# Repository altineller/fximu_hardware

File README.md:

### fximu_hardware

Hardware files for FXIMU project.

**Project main repository: https://github.com/altineller/fximu**

**Project firmware repository: https://github.com/altineller/fximu_firmware**  

---
|   ||
|----|----|

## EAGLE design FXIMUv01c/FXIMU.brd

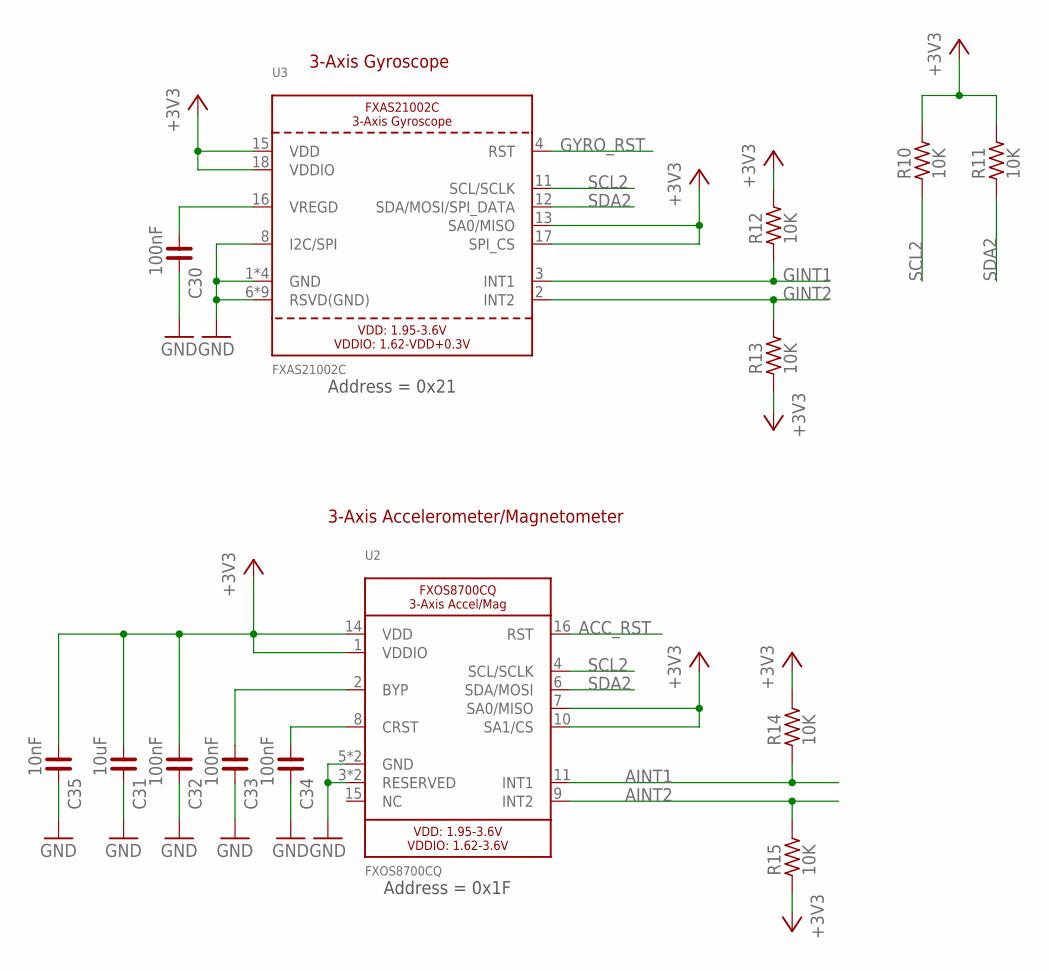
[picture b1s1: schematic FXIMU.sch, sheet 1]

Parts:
C30, C32, C33, C34: 100nF; C0402
C31: 10uF; C0603
C35: 10nF; C0402
R10, R11, R12, R13, R14, R15: 10K; R0402
U2: FXOS8700CQ; QFN16_3MM_FREESCALE_5X3
U3: FXAS21002C; QFN24_4MM_FREESCALE_7X5

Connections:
+3V3: C31.1, C32.1, C35.1, R10.2, R11.2, R12.2, R13.1, R14.2, R15.1, U2.1 (VDDIO), U2.7 (SA0/MISO), U2.10 (SA1/CS), U2.14 (VDD), U3.13 (SA0/MISO), U3.15 (VDD), U3.17 (SPI_CS), U3.18 (VDDIO); also elsewhere on the board
ACC_RST: U2.16 (RST); also elsewhere on the board
AINT1: R14.1, U2.11 (INT1); also elsewhere on the board
AINT2: R15.2, U2.9 (INT2); also elsewhere on the board
GINT1: R12.1, U3.3 (INT1); also elsewhere on the board
GINT2: R13.2, U3.2 (INT2); also elsewhere on the board
GND: C30.2, C31.2, C32.2, C33.2, C34.2, C35.2, U2.3 (RESERVED), U2.5 (GND), U2.12 (GND), U2.13 (RESERVED), U3.1 (GND), U3.5 (GND), U3.6 (RSVD(GND)), U3.7 (RSVD(GND)), U3.8 (I2C/SPI), U3.9 (RSVD(GND)), U3.10 (RSVD(GND)), U3.14 (GND), U3.19 (GND), U3.20 (RSVD(GND)), U3.21 (RSVD(GND)), U3.22 (RSVD(GND)), U3.23 (RSVD(GND)), U3.24 (RSVD(GND)); also elsewhere on the board
GYRO_RST: U3.4 (RST); also elsewhere on the board
unnamed: C30.1, U3.16 (VREGD)
unnamed: C33.1, U2.2 (BYP)
unnamed: C34.1, U2.8 (CRST)
SCL2: R10.1, U2.4 (SCL/SCLK), U3.11 (SCL/SCLK); also elsewhere on the board
SDA2: R11.1, U2.6 (SDA/MOSI), U3.12 (SDA/MOSI/SPI_DATA); also elsewhere on the board

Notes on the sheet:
Address = 0x21
Address = 0x1F
3-Axis Accelerometer/Magnetometer
3-Axis Gyroscope

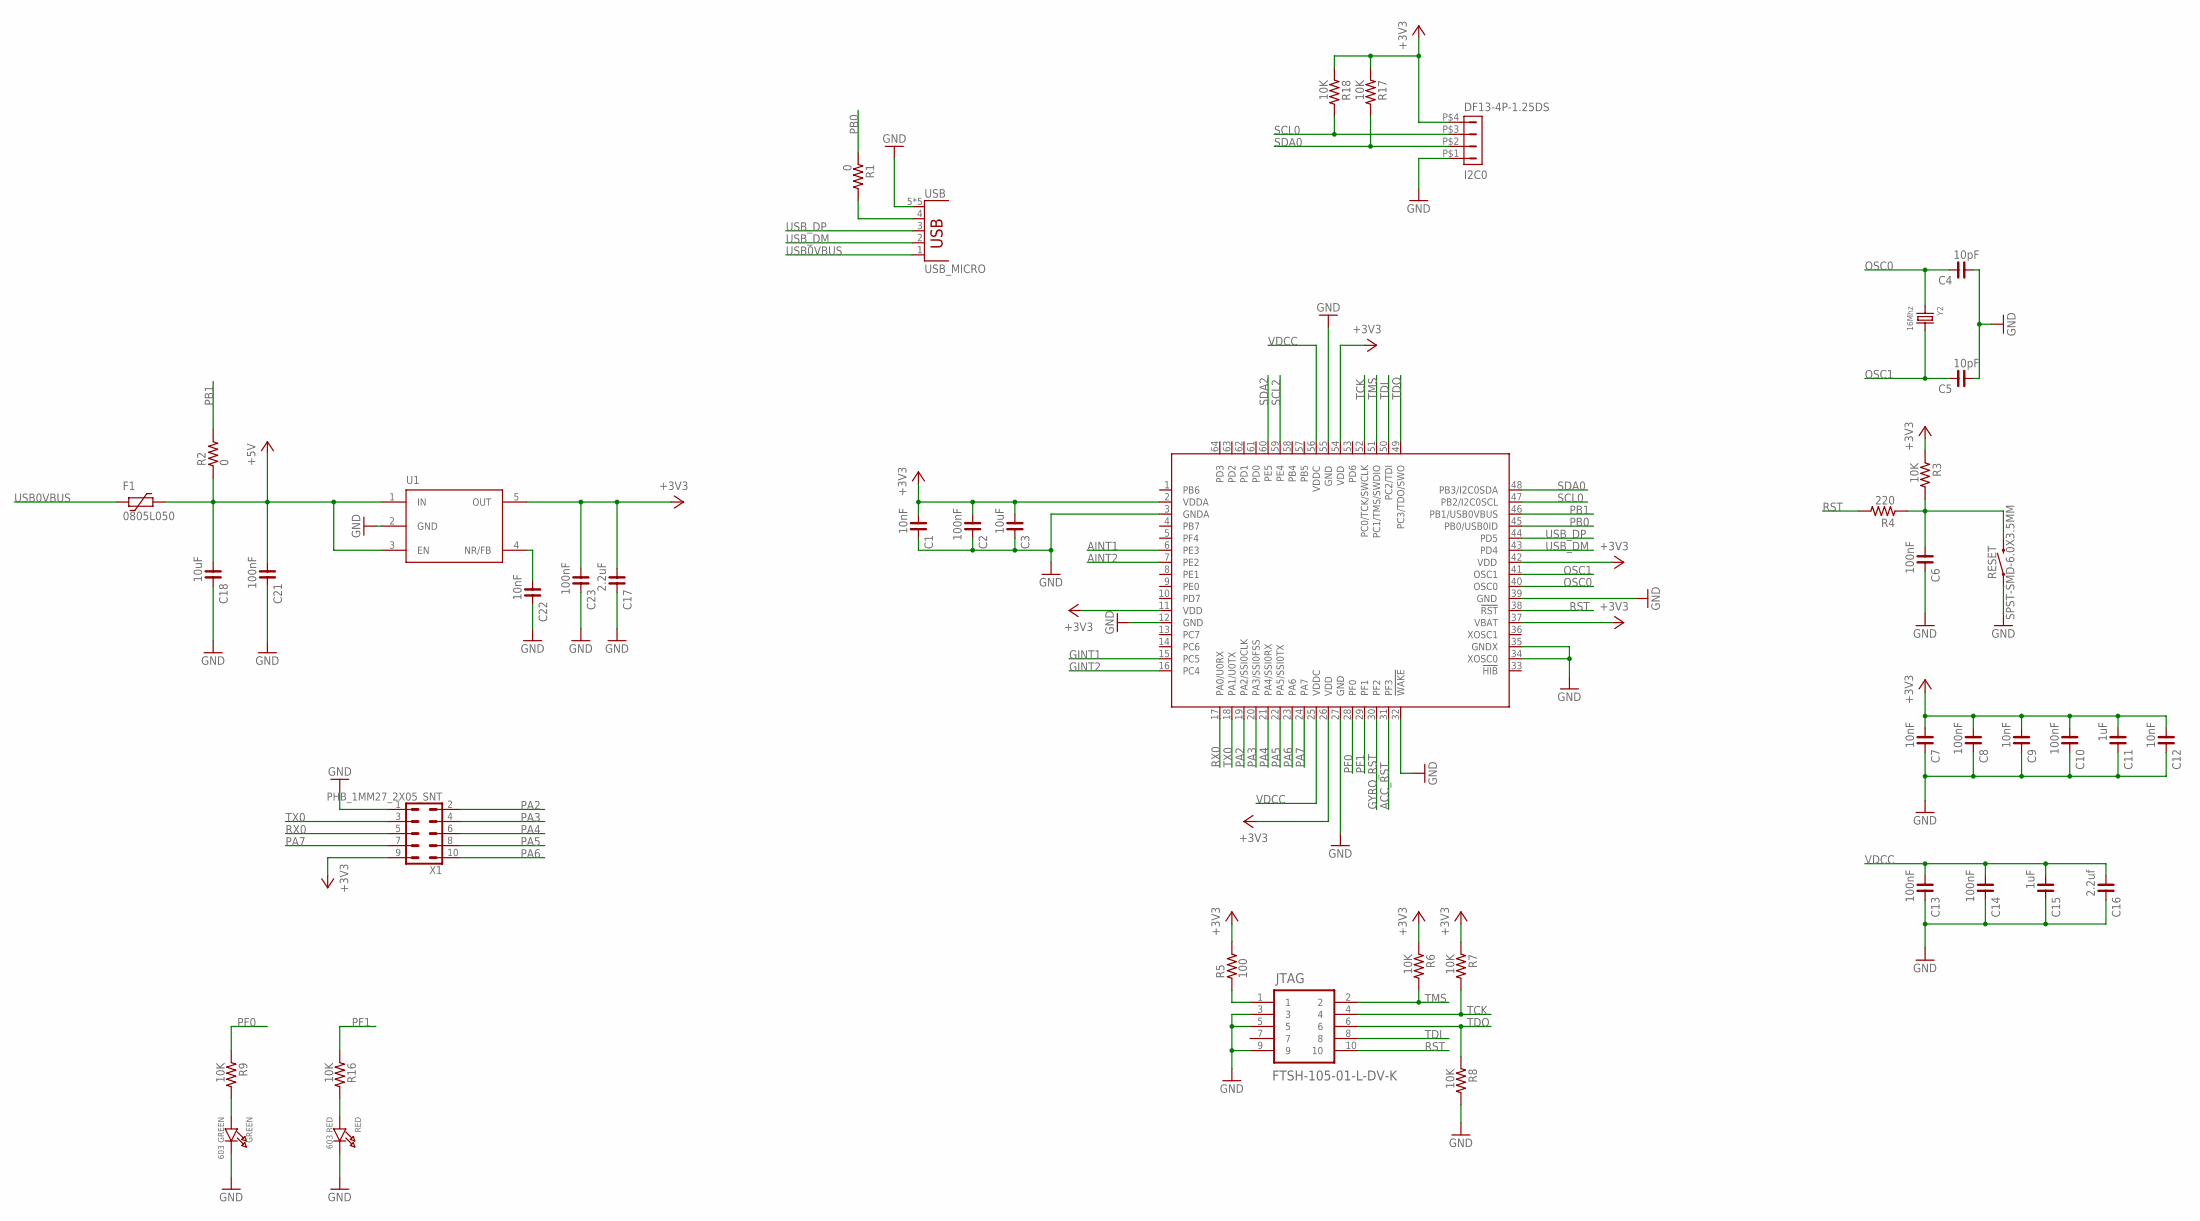
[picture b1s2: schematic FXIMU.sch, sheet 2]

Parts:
C1, C7, C9, C12, C22: 10nF; C0402
C2, C6, C8, C10, C13, C14, C21, C23: 100nF; C0402
C3, C18: 10uF; C0603
C4, C5: 10pF; C0402
C11, C15: 1uF; C0402
C16: 2.2uf; C0603
C17: 2.2uF; C0603
F1: 0805L050; 0805L
GREEN: 603 GREEN; CHIPLED_0603
I2C0: DF13-4P-1.25DS
IC1: TM4C123[7,G]XXPM; PM_S-PQFP-G64
JTAG: FTSH-105-01-L-DV-K; SAMTEC_FTSH-105-01-L-DV-K
R1, R2: 0; R0402
R3, R6, R7, R8, R9, R16, R17, R18: 10K; R0402
R4: 220; R0402
R5: 100; R0402
RED: 603 RED; CHIPLED_0603
RESET: SPST-SMD-6.0X3.5MM; TACTILE_SWITCH_SMD_6.0X3.5MM
U1: TPS73633; SOT23-5L
USB: USB_MICRO; USB_MICRO_MOLEX_FULL
X1: PHB_1MM27_2X05_SNT
Y2: 16Mhz; 6X3.3MM

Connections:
+3V3: C1.1, C2.1, C3.1, C7.1, C8.1, C9.1, C10.1, C11.1, C12.1, C17.1, C23.1, I2C0.P$4 (4), IC1.2 (VDDA), IC1.11 (VDD), IC1.26 (VDD), IC1.37 (VBAT), IC1.42 (VDD), IC1.54 (VDD), R3.1, R5.2, R6.1, R7.1, R17.1, R18.1, U1.5 (OUT), X1.9; also elsewhere on the board
+5V: C18.1, C21.1, F1.1, R2.1, U1.1 (IN), U1.3 (EN)
ACC_RST: IC1.31 (PF3); also elsewhere on the board
AINT1: IC1.6 (PE3); also elsewhere on the board
AINT2: IC1.7 (PE2); also elsewhere on the board
GINT1: IC1.15 (PC5); also elsewhere on the board
GINT2: IC1.16 (PC4); also elsewhere on the board
GND: C1.2, C2.2, C3.2, C4.1, C5.1, C6.2, C7.2, C8.2, C9.2, C10.2, C11.2, C12.2, C13.2, C14.2, C15.2, C16.2, C17.2, C18.2, C21.2, C22.2, C23.2, GREEN.C, I2C0.P$1 (1), IC1.3 (GNDA), IC1.12 (GND), IC1.27 (GND), IC1.32 (!WAKE), IC1.34 (XOSC0), IC1.35 (GNDX), IC1.39 (GND), IC1.55 (GND), JTAG.3, JTAG.5, JTAG.9, R8.2, RED.C, RESET.1, U1.2 (GND), USB.5 (GND), USB.P$1 (GND), USB.P$2 (GND), USB.P$3 (GND), USB.P$4 (GND), X1.1; also elsewhere on the board
GYRO_RST: IC1.30 (PF2); also elsewhere on the board
unnamed: JTAG.1, R5.1
unnamed: C6.1, R3.2, R4.1, RESET.2
unnamed: GREEN.A, R9.2
unnamed: R1.2, USB.4 (ID)
unnamed: R16.2, RED.A
unnamed: C22.1, U1.4 (NR/FB)
OSC0: C4.2, IC1.40 (OSC0), Y2.1
OSC1: C5.2, IC1.41 (OSC1), Y2.2
PA2: IC1.19 (PA2/SSI0CLK), X1.2
PA3: IC1.20 (PA3/SSI0FSS), X1.4
PA4: IC1.21 (PA4/SSI0RX), X1.6
PA5: IC1.22 (PA5/SSI0TX), X1.8
PA6: IC1.23 (PA6), X1.10
PA7: IC1.24 (PA7), X1.7
PB0: IC1.45 (PB0/USB0ID), R1.1
PB1: IC1.46 (PB1/USB0VBUS), R2.2
PF0: IC1.28 (PF0), R9.1
PF1: IC1.29 (PF1), R16.1
RST: IC1.38 (!RST), JTAG.10, R4.2
RX0: IC1.17 (PA0/U0RX), X1.5
SCL0: I2C0.P$3 (3), IC1.47 (PB2/I2C0SCL), R18.2
SCL2: IC1.59 (PE4); also elsewhere on the board
SDA0: I2C0.P$2 (2), IC1.48 (PB3/I2C0SDA), R17.2
SDA2: IC1.60 (PE5); also elsewhere on the board
TCK: IC1.52 (PC0/TCK/SWCLK), JTAG.4, R7.2
TDI: IC1.50 (PC2/TDI), JTAG.8
TDO: IC1.49 (PC3/TDO/SWO), JTAG.6, R8.1
TMS: IC1.51 (PC1/TMS/SWDIO), JTAG.2, R6.2
TX0: IC1.18 (PA1/U0TX), X1.3
USB0VBUS: F1.2, USB.1 (VBUS)
USB_DM: IC1.43 (PD4), USB.2 (D-)
USB_DP: IC1.44 (PD5), USB.3 (D+)
VDCC: C13.1, C14.1, C15.1, C16.1, IC1.25 (VDDC), IC1.56 (VDDC)

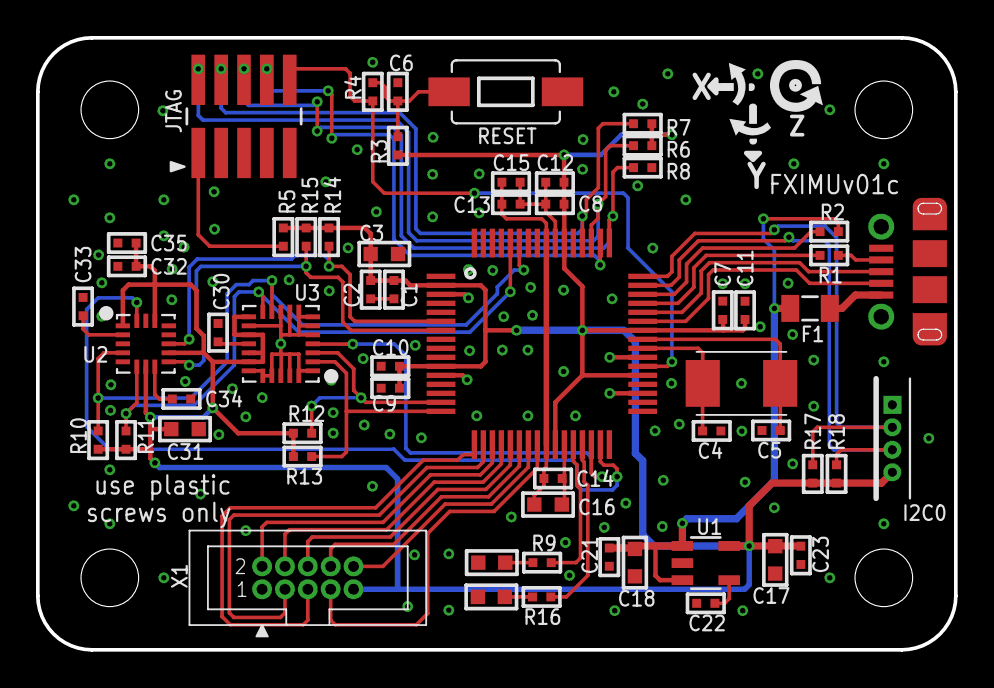
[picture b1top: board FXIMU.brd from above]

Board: 2 copper layers, 51.0 x 34.0 mm, 61 parts (0 on the bottom side), 45 nets.

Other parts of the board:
U$27: SYMBOL_GYRO_CCLOCKWISE
U$28: SYMBOL_GYRO_CLOCKWISE
U$31: SYMBOL_GYRO_Z

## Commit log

2020-07-01 Create t
2020-07-01 fximu v01c eagle files
2020-07-01 create dir
2020-07-01 Gerber files added
2021-03-16 license update

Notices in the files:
parts and their libraries:
microbuilder: This work is placed in the public domain, and may be freely used for commercial and non-commercial work with the following conditions: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
rc-master-smd: Copyright (C) 2007, Bob Starr
